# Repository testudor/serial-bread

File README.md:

# Serial Bread

This is part of the "Modular Breadboard" parent project. 

It's a basic USB-to-UART adapter with a robust USB-C connector and switchable logic levels. It can also provide up to 3A@5v and 600mA@3<area>.3V for your project.
<!-- <area> prevents auto link generation caused by .3V -->

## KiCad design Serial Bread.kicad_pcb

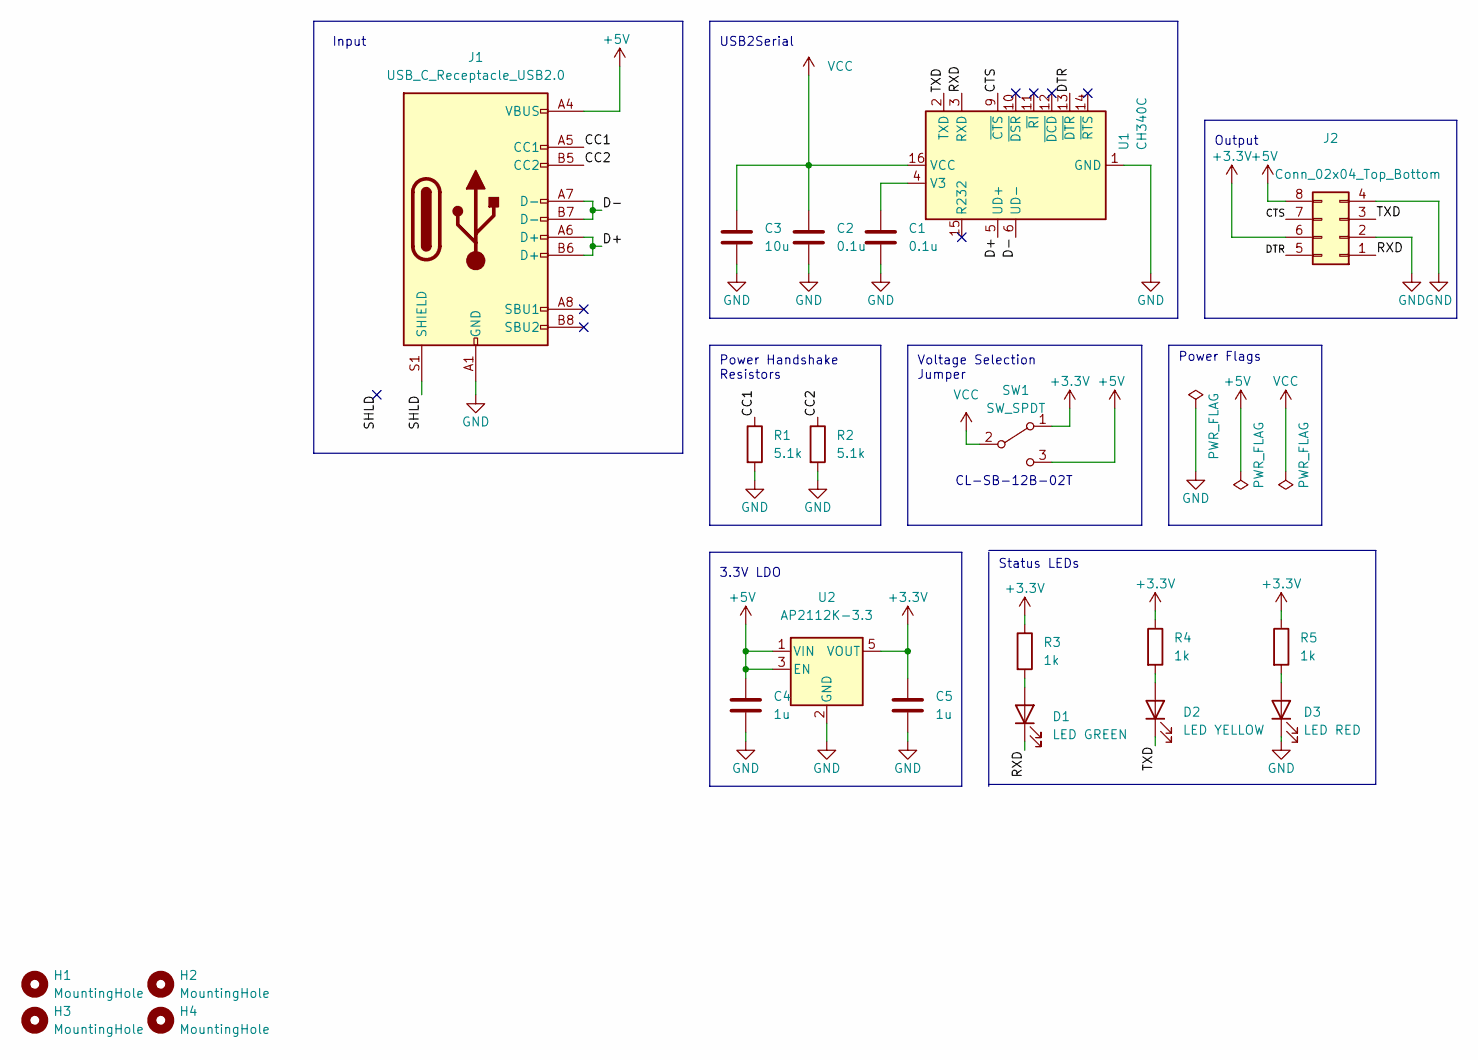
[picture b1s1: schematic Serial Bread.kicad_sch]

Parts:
C1, C2: 0.1u; C_0402_1005Metric; MPN C1525
C3: 10u; C_0402_1005Metric; MPN C15525
C4, C5: 1u; C_0402_1005Metric; MPN C52923
D1: LED GREEN; LED_0603_1608Metric; MPN C72043
D2: LED YELLOW; LED_0603_1608Metric; MPN C72038
D3: LED RED; LED_0603_1608Metric; MPN C2286
H1, H2, H3, H4: MountingHole; MountingHole_2.7mm_M2.5_ISO14580_Pad_TopBottom
J1: USB_C_Receptacle_USB2.0; USB_C_Receptacle_HRO_TYPE-C-31-M-12; MPN C165948
J2: Conn_02x04_Top_Bottom; PinSocket_2x04_P2.54mm_Vertical; MPN C358726
R1, R2: 5.1k; R_0402_1005Metric; MPN C25905
R3, R4, R5: 1k; R_0402_1005Metric; MPN C11702
SW1: SW_SPDT; CL-SB-12B-02T; MPN C2921648
U1: CH340C; SOIC-16_3.9x9.9mm_P1.27mm; MPN C84681
U2: AP2112K-3.3; SOT-23-5; MPN C51118

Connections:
+3.3V: C5.2, J2.6, R3.1, R4.1, R5.1, SW1.1 (A), U2.5 (VOUT)
+5V: C4.2, J1.A4 (VBUS), J1.A9 (VBUS), J1.B4 (VBUS), J1.B9 (VBUS), J2.8, SW1.3 (C), U2.1 (VIN), U2.3 (EN)
/CC1: J1.A5 (CC1), R1.1
/CC2: J1.B5 (CC2), R2.1
/CTS: J2.7, U1.9 (~CTS)
/D+: J1.A6 (D+), J1.B6 (D+), U1.5 (UD+)
/D-: J1.A7 (D-), J1.B7 (D-), U1.6 (UD-)
/DTR: J2.5, U1.13 (~DTR)
/RXD: D1.1 (K), J2.1, U1.3 (RXD)
/SHLD: J1.S1 (SHIELD)
/TXD: D2.1 (K), J2.3, U1.2 (TXD)
GND: C1.1, C2.1, C3.1, C4.1, C5.1, D3.1 (K), J1.A1 (GND), J1.A12 (GND), J1.B1 (GND), J1.B12 (GND), J2.2, J2.4, R1.2, R2.2, U1.1 (GND), U2.2 (GND)
unnamed: D1.2 (A), R3.2
unnamed: D2.2 (A), R4.2
unnamed: D3.2 (A), R5.2
unnamed: C1.2, U1.4 (V3)
VCC: C2.2, C3.2, SW1.2 (B), U1.16 (VCC)

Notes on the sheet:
Power Flags
CL-SB-12B-02T
Output
Power Handshake Resistors
Input
Voltage Selection Jumper
USB2Serial
Status LEDs
3.3V LDO

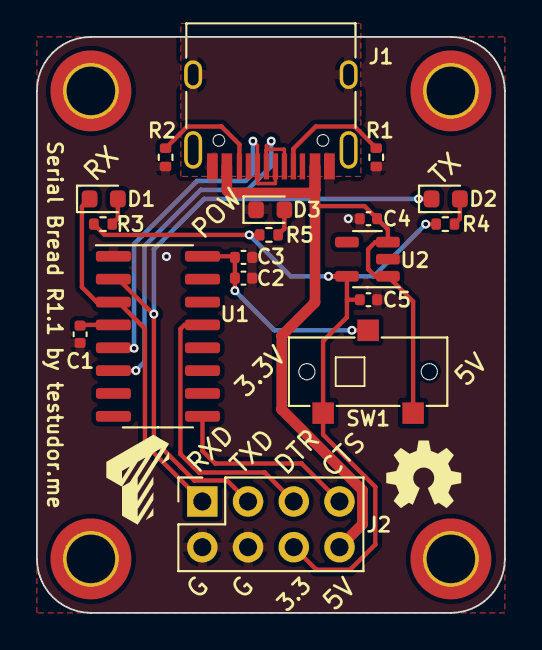
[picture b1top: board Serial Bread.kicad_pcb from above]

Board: 2 copper layers, 26.0 x 32.0 mm, 22 parts (0 on the bottom side), 16 nets.

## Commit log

2022-12-31 change keepout zone display
2023-01-09 make copper fill clearance consistent
2023-01-09 Add missing pcbdraw modules
2023-01-09 make silkscreen consistent
2023-01-10 Add readma + images
2023-01-10 Prevent link generation
2023-01-10 Add PCB side labels
2023-01-11 Add license
2023-01-15 add kibot workflow for DRC & ERC testing
2023-01-15 Exlude some DRC violations so action succeeds
2023-11-04 Initial commit R1.1
2024-01-09 Fixed missing OSHW silk
2024-01-09 Added panel config
2024-01-09 Migrate kibot to V7
2024-02-14 Add DRC exclusions to prevent overzealous warnings
2024-02-14 Disable actions because they are broken. Pinky promise I'll always check it manually
2024-02-14 Add new image to README
2024-02-14 Revert "Migrate kibot to V7"
    This reverts commit a3272a681c647fefaa0c146f274253911f889e1f.
2024-02-14 Revert "Add DRC exclusions to prevent overzealous warnings"
    This reverts commit 4dcb820638929961085c7ca255224868a753fc75.
2024-02-14 Revert "Fixed missing OSHW silk"
    This reverts commit 2a56d455a99e7c22cc2508ea68d32a0d58d2fe36.
2024-02-14 Revert "Initial commit R1.1"
    This reverts commit dbca94149cb8df2c718ea664c1760d3caefabc82.
2024-02-14 Revert "Added panel config"
    This reverts commit a0ae4490247bcf68e783aedebf1b2026729a3600.
2024-02-14 Revert "Disable actions because they are broken. Pinky promise I'll always check it manually"
    This reverts commit 22386aef562a3ad52172a3ae1301e8e8034a9d3b.
